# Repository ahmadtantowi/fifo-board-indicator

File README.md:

# FIFO Board Indicator

A FIFO box indicator board utilizing LED lamps to visually guide users on the order of box usage.

## Wokwi Simulation (wokwi/diagram.json)

This project contains a Wokwi diagram file at `wokwi/diagram.json` plus a detailed guide at `wokwi/README.md`. Important: the `diagram.json` in this repository describes the simulated hardware wiring and components only — it does NOT include the firmware/sketch by default.

Visit [the Wokwi project](https://wokwi.com/projects/449662087423426561) to see the simulation in action.

Below is a screenshot of the Wokwi editor showing the loaded diagram.

# Development Environment Setup

This guide explains how to set up and build the project using PlatformIO CLI and how to generate a `compile_commands.json` (compiledb) file so your editor's C/C++ language server (clangd / IntelliSense) can find Arduino and library headers (e.g. `Wire.h`, `Adafruit_GFX.h`, etc.).

This repository target platform: `esp32-s3-devkitc-1` with `framework = arduino`.

## Prerequisites

- Python 3.7+ (for PlatformIO CLI)
- Git (optional but recommended)
- A terminal (macOS / Linux / Windows PowerShell / Windows CMD)
- An editor (VS Code, Zed, or other). If you use VS Code with the PlatformIO extension, some intellisense steps below are optional.

## 1) Install PlatformIO CLI

See [PlatformIO Installation Guide](https://docs.platformio.org/en/latest/core/installation/index.html) and install the Shell Commands, so you can run `pio` from the terminal.

## 2) Ensure `platformio.ini` is configured

Open `platformio.ini` and make sure:
- `framework = arduino` is present.
- Required libraries are declared under `lib_deps` or installed via `pio lib install`.

A minimal example `platformio.ini` snippet (this project already includes one — if you modify it, ensure you add the libraries your code uses):

```/dev/null/platformio.ini#L1-40
[env:esp32-s3-devkitc-1]
platform = espressif32
board = esp32-s3-devkitc-1
framework = arduino
lib_deps =
  adafruit/Adafruit GFX Library
  adafruit/Adafruit SSD1306
  Keypad
```

If you prefer to install libraries manually (instead of relying on `lib_deps`), run:

```/dev/null/commands.sh#L1-6
pio lib install "Adafruit GFX Library"
pio lib install "Adafruit SSD1306"
pio lib install "Keypad"
```

Running `pio lib install` will add libraries to the project `.pio/libdeps` folder (or to the global library storage depending on your settings). Using `lib_deps` in `platformio.ini` lets PlatformIO fetch them automatically during `pio run`.

## 3) Build the project

From the project root (the directory containing `platformio.ini`):

```/dev/null/commands.sh#L1-4
# Build
pio run

# If you want verbose output (helps debugging missing headers)
pio run -v
```

Successful build output ends with a message like "Building . . . SUCCESS" and a `/.pio/build/<env>` folder with compiled objects.

Common build errors and how to fix them:
- `fatal error: Wire.h: No such file or directory`
  - Ensure `framework = arduino` is present in `platformio.ini`.
  - Ensure the proper board is set (so framework/toolchain selected is correct).
  - Make sure the Adafruit/Arduino libraries are installed (see `lib_deps` or run `pio lib install`).
  - Run `pio run -v` to see include paths and confirm where the compiler is looking.

- Missing `Adafruit_GFX.h` or `Keypad.h`:
  - Verify `lib_deps` contains those libraries OR install them manually via `pio lib install`.
  - After installing, run `pio run` again.

If things look stale, try cleaning and rebuilding:

```/dev/null/commands.sh#L1-6
pio run --target clean
rm -rf .pio/build .pio/libdeps .pio/.cache  # careful: removes PlatformIO caches
pio run
```

## 4) Generate `compile_commands.json` for editor intellisense (Optional, but recommended)

Many language servers (clangd, ccls) and editors accept a `compile_commands.json` database that contains the compile flags and include paths for each translation unit. PlatformIO can generate it for you.

```/dev/null/commands.sh#L1-6
# From project root
pio run --target compiledb
# This produces a compile_commands.json (or a json in .pio) in the project root.
```

What this does:
- Produces `compile_commands.json` that tools like clangd use to get the exact include paths and flags used by PlatformIO.
- This resolves editor diagnostics such as "Wire.h not found" and other header resolution issues.

Editor-specific notes:
- VS Code with the official PlatformIO extension: compiledb is typically not required because the extension already configures IntelliSense. Still, generating `compile_commands.json` is harmless and can help external tools.
- Zed or other editors using `clangd`: after generating `compile_commands.json`, restart your editor or the language server so it picks the file up and re-indexes the project.

## 5) Editor integration / clangd troubleshooting (Zed, others)

If your editor still shows `Wire.h` or other "file not found" diagnostics after generating the compiledb:

1. Confirm `compile_commands.json` exists in the project root.
2. Restart the editor / language server (e.g., reload window).
3. Confirm the language server is configured to look for `compile_commands.json` in the project root. clangd normally auto-detects it.
4. If your editor has a caching layer, clear or re-index the project.

## 6) Extra PlatformIO commands that help diagnose issues

```/dev/null/commands.sh#L1-12
# Show project environments and targets
pio project inspect

# Show installed libs
pio lib list

# Force update of platform and libraries
pio update

# Remove and reinstall libs
pio lib uninstall <LIBNAME>
pio lib install <LIBNAME>
```

## 7) Example quick checklist to get to a successful `pio run`

1. Ensure Python is installed and `pio` works:
   ```/dev/null/commands.sh#L1-4
   python3 -m pip install -U platformio
   pio --version
   ```
2. Confirm `platformio.ini` includes `framework = arduino` and (optionally) `lib_deps`.
3. Install libraries if needed:
   ```/dev/null/commands.sh#L1-3
   pio lib install "Adafruit GFX Library"
   pio lib install "Adafruit SSD1306"
   pio lib install "Keypad"
   ```
4. Build:
   ```/dev/null/commands.sh#L1-3
   pio run
   ```
5. If editor diagnostics show missing headers, generate compiledb:
   ```/dev/null/commands.sh#L1-2
   pio run --target compiledb
   # Restart editor / language server
   ```

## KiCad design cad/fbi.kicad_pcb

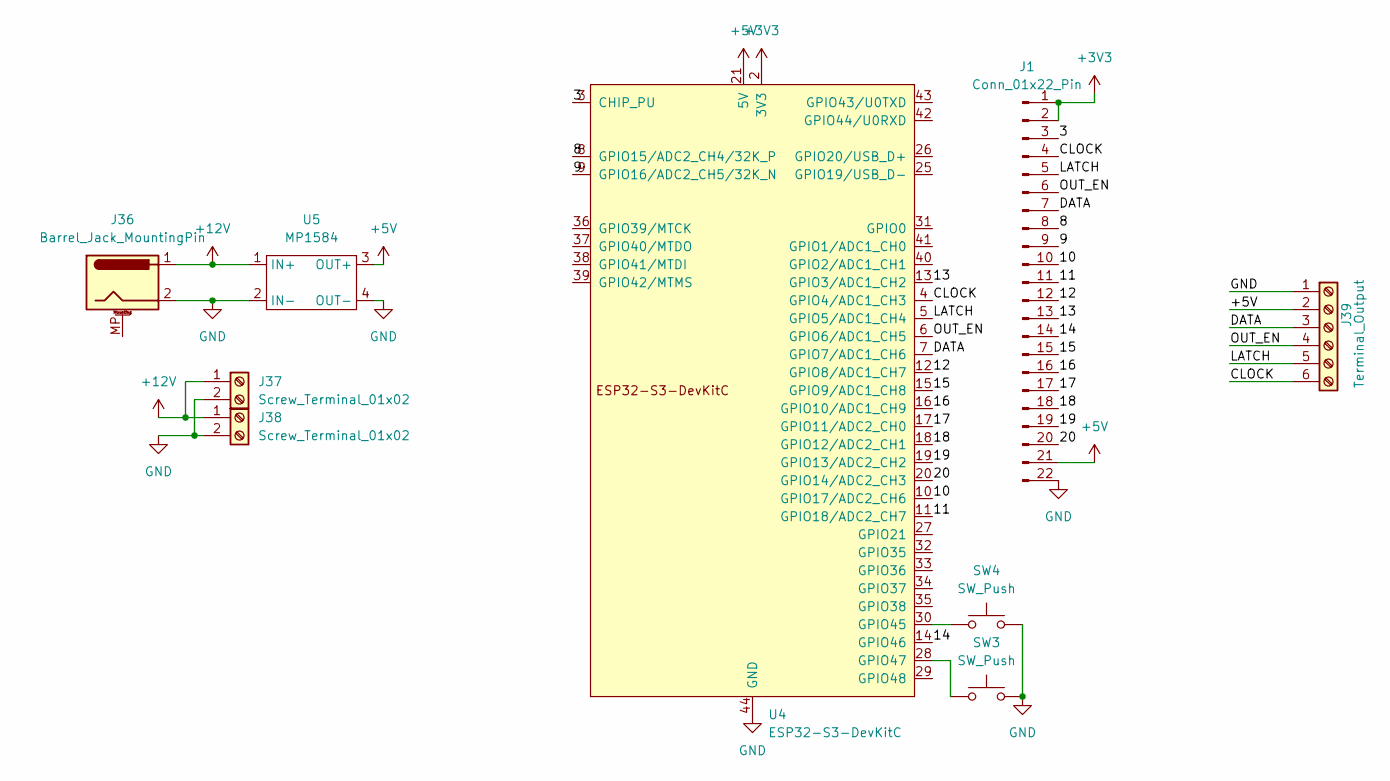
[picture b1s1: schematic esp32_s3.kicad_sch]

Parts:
J1: Conn_01x22_Pin; PinSocket_1x22_P2.54mm_Vertical
J36: Barrel_Jack_MountingPin; BarrelJack_Horizontal
J37, J38: Screw_Terminal_01x02; TerminalBlock_MaiXu_MX126-5.0-02P_1x02_P5.00mm
J39: Terminal_Output; TerminalBlock_Xinya_XY308-2.54-6P_1x06_P2.54mm_Horizontal
SW3, SW4: SW_Push; SW_PUSH_6mm
U4: ESP32-S3-DevKitC
U5: MP1584; MP1584-Module_B22.1x16.8mm

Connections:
+3V3: J1.1, J1.2, U4.1 (3V3), U4.2 (3V3)
+5V: J1.21, J39.2, U4.21 (5V), U5.3 (OUT+); also elsewhere on the board
+12V: J36.1, J37.1, J38.1, U5.1 (IN+)
/ESP32-S3/3: J1.3, U4.3 (CHIP_PU)
/ESP32-S3/8: J1.8, U4.8 (GPIO15/ADC2_CH4/32K_P)
/ESP32-S3/9: J1.9, U4.9 (GPIO16/ADC2_CH5/32K_N)
/ESP32-S3/10: J1.10, U4.10 (GPIO17/ADC2_CH6)
/ESP32-S3/11: J1.11, U4.11 (GPIO18/ADC2_CH7)
/ESP32-S3/12: J1.12, U4.12 (GPIO8/ADC1_CH7)
/ESP32-S3/13: J1.13, U4.13 (GPIO3/ADC1_CH2)
/ESP32-S3/14: J1.14, U4.14 (GPIO46)
/ESP32-S3/15: J1.15, U4.15 (GPIO9/ADC1_CH8)
/ESP32-S3/16: J1.16, U4.16 (GPIO10/ADC1_CH9)
/ESP32-S3/17: J1.17, U4.17 (GPIO11/ADC2_CH0)
/ESP32-S3/18: J1.18, U4.18 (GPIO12/ADC2_CH1)
/ESP32-S3/19: J1.19, U4.19 (GPIO13/ADC2_CH2)
/ESP32-S3/20: J1.20, U4.20 (GPIO14/ADC2_CH3)
/ESP32-S3/CLOCK: J1.4, J39.6, U4.4 (GPIO4/ADC1_CH3)
/ESP32-S3/DATA: J1.7, J39.3, U4.7 (GPIO7/ADC1_CH6)
/ESP32-S3/LATCH: J1.5, J39.5, U4.5 (GPIO5/ADC1_CH4)
/ESP32-S3/OUT_EN: J1.6, J39.4, U4.6 (GPIO6/ADC1_CH5)
GND: J1.22, J36.2, J37.2, J38.2, J39.1, SW3.2, SW4.2, U4.22 (GND), U4.23 (GND), U4.24 (GND), U4.44 (GND), U5.2 (IN-), U5.4 (OUT-); also elsewhere on the board
unnamed: SW3.1, U4.28 (GPIO47)

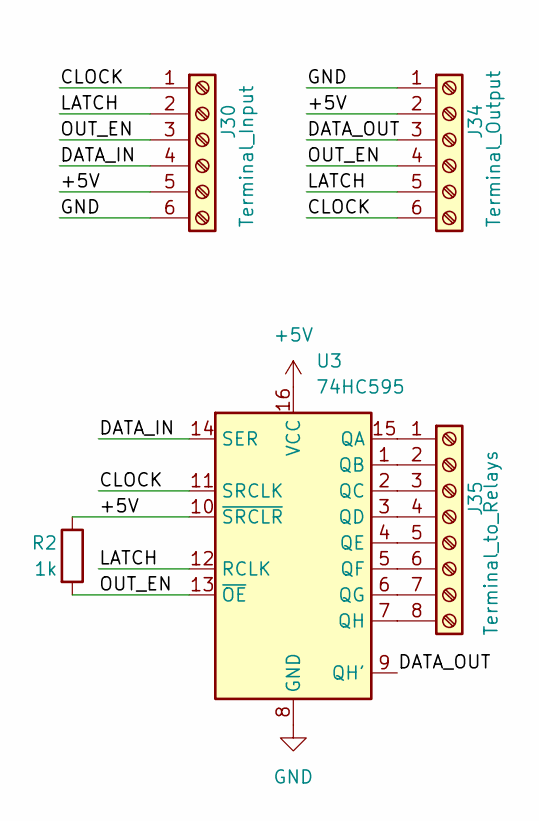
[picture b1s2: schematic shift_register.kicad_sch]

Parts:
J30: Terminal_Input; TerminalBlock_Xinya_XY308-2.54-6P_1x06_P2.54mm_Horizontal
J34: Terminal_Output; TerminalBlock_Xinya_XY308-2.54-6P_1x06_P2.54mm_Horizontal
J35: Terminal_to_Relays; TerminalBlock_MaiXu_MX126-5.0-08P_1x08_P5.00mm
R2: 1k; R_Axial_DIN0204_L3.6mm_D1.6mm_P7.62mm_Horizontal
U3: 74HC595; DIP-16_W7.62mm_Socket

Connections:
+5V: J30.5, J34.2, R2.1, U3.10 (~SRCLR), U3.16 (VCC); also elsewhere on the board
/Shift Register/CLOCK: J30.1, J34.6, U3.11 (SRCLK)
/Shift Register/DATA_IN: J30.4, U3.14 (SER)
/Shift Register/DATA_OUT: J34.3, U3.9 (QH')
/Shift Register/LATCH: J30.2, J34.5, U3.12 (RCLK)
/Shift Register/OUT_EN: J30.3, J34.4, R2.2, U3.13 (~OE)
GND: J30.6, J34.1, U3.8 (GND); also elsewhere on the board
unnamed: J35.1, U3.15 (QA)
unnamed: J35.2, U3.1 (QB)
unnamed: J35.3, U3.2 (QC)
unnamed: J35.4, U3.3 (QD)
unnamed: J35.5, U3.4 (QE)
unnamed: J35.6, U3.5 (QF)
unnamed: J35.7, U3.6 (QG)
unnamed: J35.8, U3.7 (QH)

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
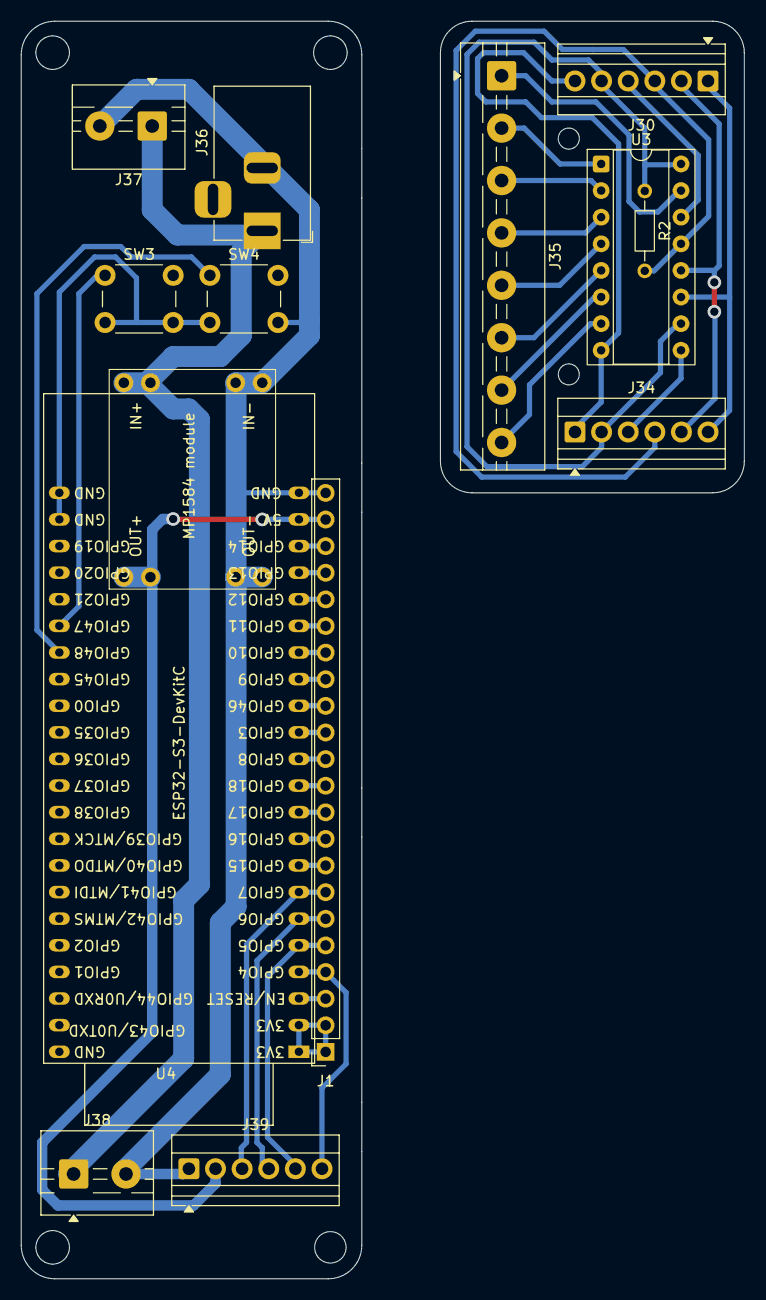
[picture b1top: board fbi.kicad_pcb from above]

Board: 2 copper layers, 69.0 x 120.0 mm, 14 parts (0 on the bottom side), 37 nets.

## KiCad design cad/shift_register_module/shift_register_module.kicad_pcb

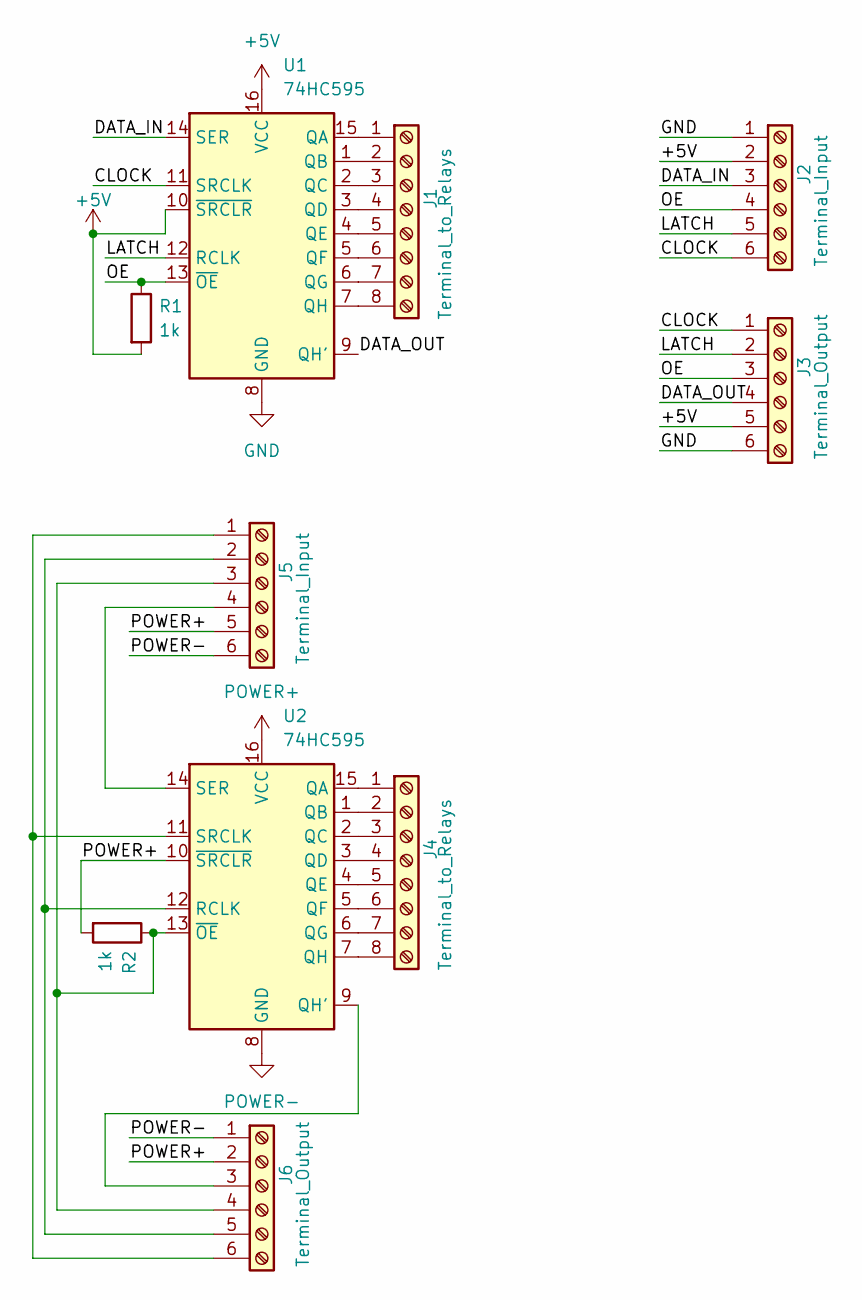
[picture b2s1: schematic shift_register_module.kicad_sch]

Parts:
J1, J4: Terminal_to_Relays; TerminalBlock_MaiXu_MX126-5.0-08P_1x08_P5.00mm
J2, J5: Terminal_Input; TerminalBlock_Xinya_XY308-2.54-6P_1x06_P2.54mm_Horizontal
J3, J6: Terminal_Output; TerminalBlock_Xinya_XY308-2.54-6P_1x06_P2.54mm_Horizontal
R1, R2: 1k; R_Axial_DIN0204_L3.6mm_D1.6mm_P7.62mm_Horizontal
U1, U2: 74HC595; DIP-16_W7.62mm_LongPads

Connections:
+5V: J2.2, J3.5, R1.2, U1.10 (~SRCLR), U1.16 (VCC)
/CLOCK: J2.6, J3.1, U1.11 (SRCLK)
/DATA_IN: J2.3, U1.14 (SER)
/DATA_OUT: J3.4, U1.9 (QH')
/LATCH: J2.5, J3.2, U1.12 (RCLK)
/OE: J2.4, J3.3, R1.1, U1.13 (~OE)
GND: J2.1, J3.6, U1.8 (GND)
unnamed: J1.1, U1.15 (QA)
unnamed: J1.2, U1.1 (QB)
unnamed: J1.3, U1.2 (QC)
unnamed: J1.4, U1.3 (QD)
unnamed: J1.5, U1.4 (QE)
unnamed: J1.6, U1.5 (QF)
unnamed: J1.7, U1.6 (QG)
unnamed: J1.8, U1.7 (QH)
unnamed: J4.1, U2.15 (QA)
unnamed: J4.2, U2.1 (QB)
unnamed: J4.3, U2.2 (QC)
unnamed: J4.4, U2.3 (QD)
unnamed: J4.5, U2.4 (QE)
unnamed: J4.6, U2.5 (QF)
unnamed: J4.7, U2.6 (QG)
unnamed: J4.8, U2.7 (QH)
unnamed: J5.1, J6.6, U2.11 (SRCLK)
unnamed: J5.2, J6.5, U2.12 (RCLK)
unnamed: J5.3, J6.4, R2.1, U2.13 (~OE)
unnamed: J5.4, U2.14 (SER)
unnamed: J6.3, U2.9 (QH')
POWER+: J5.5, J6.2, R2.2, U2.10 (~SRCLR), U2.16 (VCC)
POWER-: J5.6, J6.1, U2.8 (GND)

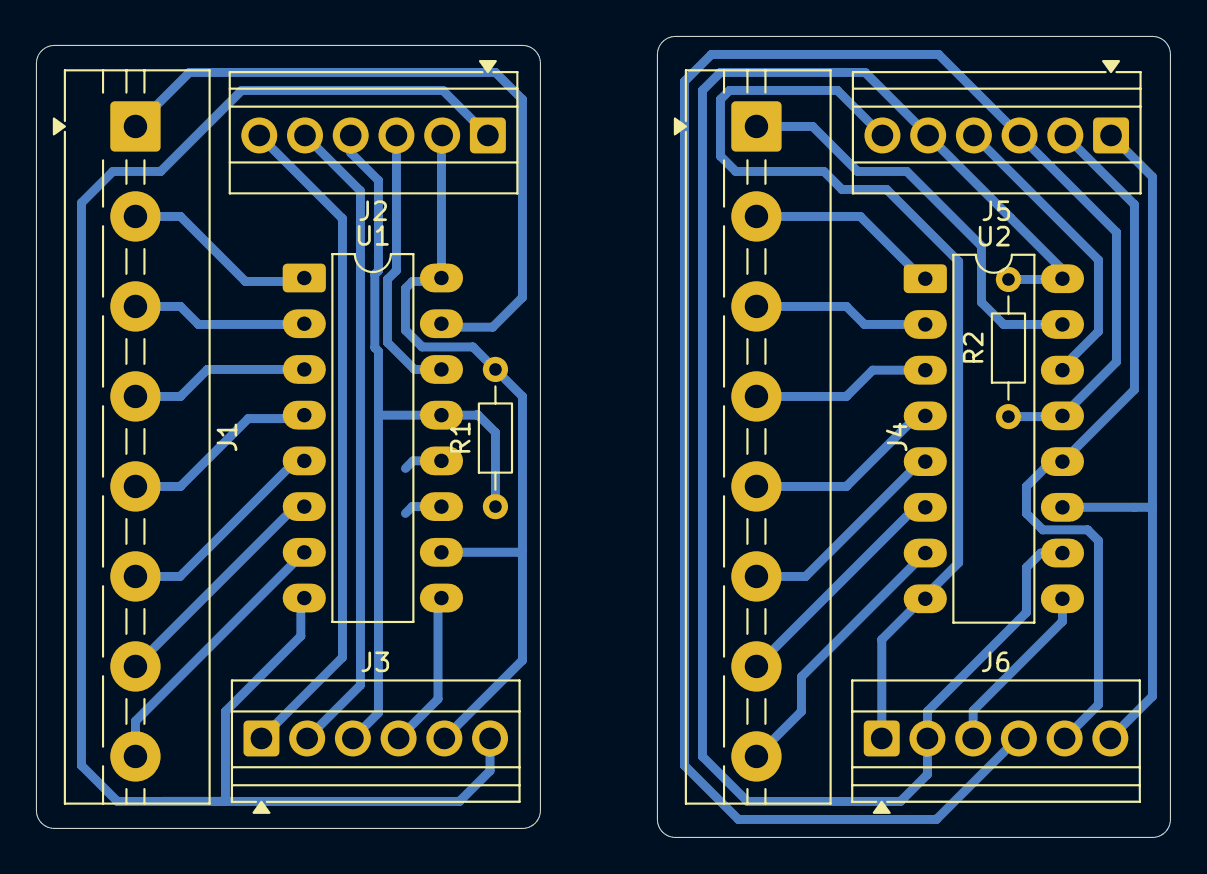
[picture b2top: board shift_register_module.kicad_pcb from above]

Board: 2 copper layers, 63.0 x 44.5 mm, 10 parts (0 on the bottom side), 30 nets.

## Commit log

2025-12-07 Add PlatformIO project skeleton and firmware
2025-12-07 Add Wokwi schematic with 224 relays and ESP32
2025-12-07 Add Wokwi preview and update diagram JSON
    Add screenshot and save diagram JSON to assets for quick access.
    Simplify and reorganize wokwi/diagram.json: rename parts (esp→esp1,
    sr→sr1), remove many relay modules, add OLED, keypad, LEDs, VCC/GND,
    update connections and metadata.
2025-12-07 Add Wokwi assets and update README and diagram
2026-01-15 Enable OE pin and add shift register sweep
    Use pin 11 as OE, set it to OUTPUT and drive HIGH at startup to keep
    outputs off during initialization, then drive LOW once setup completes.
    Implement sweepShiftRegisters() to pulse each bit across all registers
    as a quick visual test and call it once after startup.
2026-01-16 Expand .gitignore for KiCad and temp files
2026-01-16 Initialized schematic and pcb design with esp-32 s3 and 74hc595 x28
2026-01-16 Fix incorrect shift register output connection
2026-01-16 Add symbol and footprint lib for MP1584 module
2026-01-16 Ignore .DS_Store file
2026-01-16 Add power source
2026-01-19 Add schema title, button and remove pin header
2026-01-19 Place components on PCB
2026-01-19 Wiring the 12v
2026-01-20 Update MP1584 module
2026-01-20 Reposition all components
2026-01-20 Change button pin
2026-01-20 WIP wiring
2026-01-21 Fixing the grid
2026-01-23 Try separate shift register module
2026-01-23 Separate shift register as a module
2026-01-24 Add esp32-s3 module
2026-01-24 Remove filled zone
2026-01-24 Remove old design
2026-01-25 Add mounting holes for shift register module
2026-01-25 Remove unused modules
2026-01-26 More wide on wire and replace mounting hole with circles
2026-01-26 Make PCB ready to print
2026-01-26 Adjust to accept extra female pin header
2026-01-31 Make push button active low
2026-02-05 Set board constraints
2026-02-05 Change footprint for shift register IC
2026-02-05 Fix manufacture design check
    - wire width: min 0.5mm
    - space between wire: min 0.5mm
    - through hole: min 0.8mm
2026-02-06 Ignore .DS_Store files
2026-02-06 Cad design (#1)
    * Initialized schematic and pcb design with esp-32 s3 and 74hc595 x28
    * Fix incorrect shift register output connection
    * Add symbol and footprint lib for MP1584 module
    * Ignore .DS_Store file
    * Add power source
    * Add schema title, button and remove pin header
2026-02-06 Match GPIO pin with Schema design
2026-02-06 Remove OLED display and keypad component usage
2026-02-06 Add esp32-c3 board and pio multiple environments
2026-02-06 Fix indentation
2026-02-07 Connect to WiFi hotspot and MQTT server
2026-02-07 Turn relay/lamp based on message arrived from MQTT broker
2026-02-07 Blink built in LED when connecting to WiFi
2026-02-08 Refactor WiFi and MQTT connection logic with improved retry mechanisms and timeout handling
2026-02-08 Publish relay (lamp) state
2026-02-08 Better log for wifi status
2026-02-09 Change the buttons GPIO, especially GPIO48 because it used to drive internal LED
2026-02-09 Remove unused symbol
2026-02-19 Fix C3 pin mappings and move MQTT init
    Adjust BOARD_C3 pin definitions and relocate MQTT setup
    after initial LED/relay init so outputs are cleared before
    network blocking calls
2026-02-20 Separate pcb for print
2026-06-02 Update pin assignments for BOARD_S3
